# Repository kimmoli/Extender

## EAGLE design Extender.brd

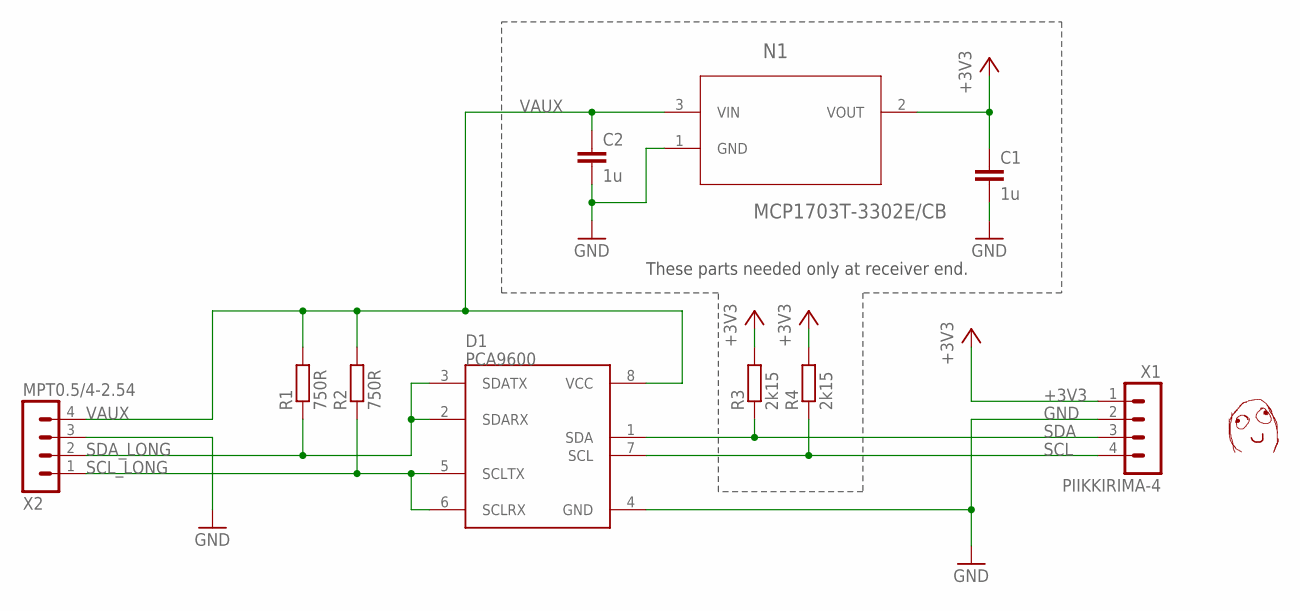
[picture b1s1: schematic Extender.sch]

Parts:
C1, C2: 1u; C0805
D1: PCA9600; SOP65P490X110-8N
N1: MCP1703T-3302E/CB; SOT95P300X145-3N
R1, R2: 750R; R0603
R3, R4: 2k15; R0603
U$1: DAFUG
X1: PIIKKIRIMA-4
X2: MPT0.5/4-2.54

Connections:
+3V3: C1.1, N1.2 (VOUT), R3.2, R4.2, X1.1
GND: C1.2, C2.2, D1.4 (GND), N1.1 (GND), X1.2, X2.3
SCL: D1.7 (SCL), R4.1, X1.4
SCL_LONG: D1.5 (SCLTX), D1.6 (SCLRX), R2.1, X2.1
SDA: D1.1 (SDA), R3.1, X1.3
SDA_LONG: D1.2 (SDARX), D1.3 (SDATX), R1.1, X2.2
VAUX: C2.1, D1.8 (VCC), N1.3 (VIN), R1.2, R2.2, X2.4

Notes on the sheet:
These parts needed only at receiver end.

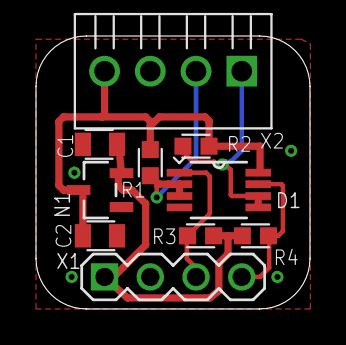
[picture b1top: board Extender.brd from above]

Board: 2 copper layers, 15.2 x 15.2 mm, 11 parts (1 on the bottom side), 7 nets.

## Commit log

2013-09-15 Silkscreen tuning
2013-09-15 Correct datasheet
